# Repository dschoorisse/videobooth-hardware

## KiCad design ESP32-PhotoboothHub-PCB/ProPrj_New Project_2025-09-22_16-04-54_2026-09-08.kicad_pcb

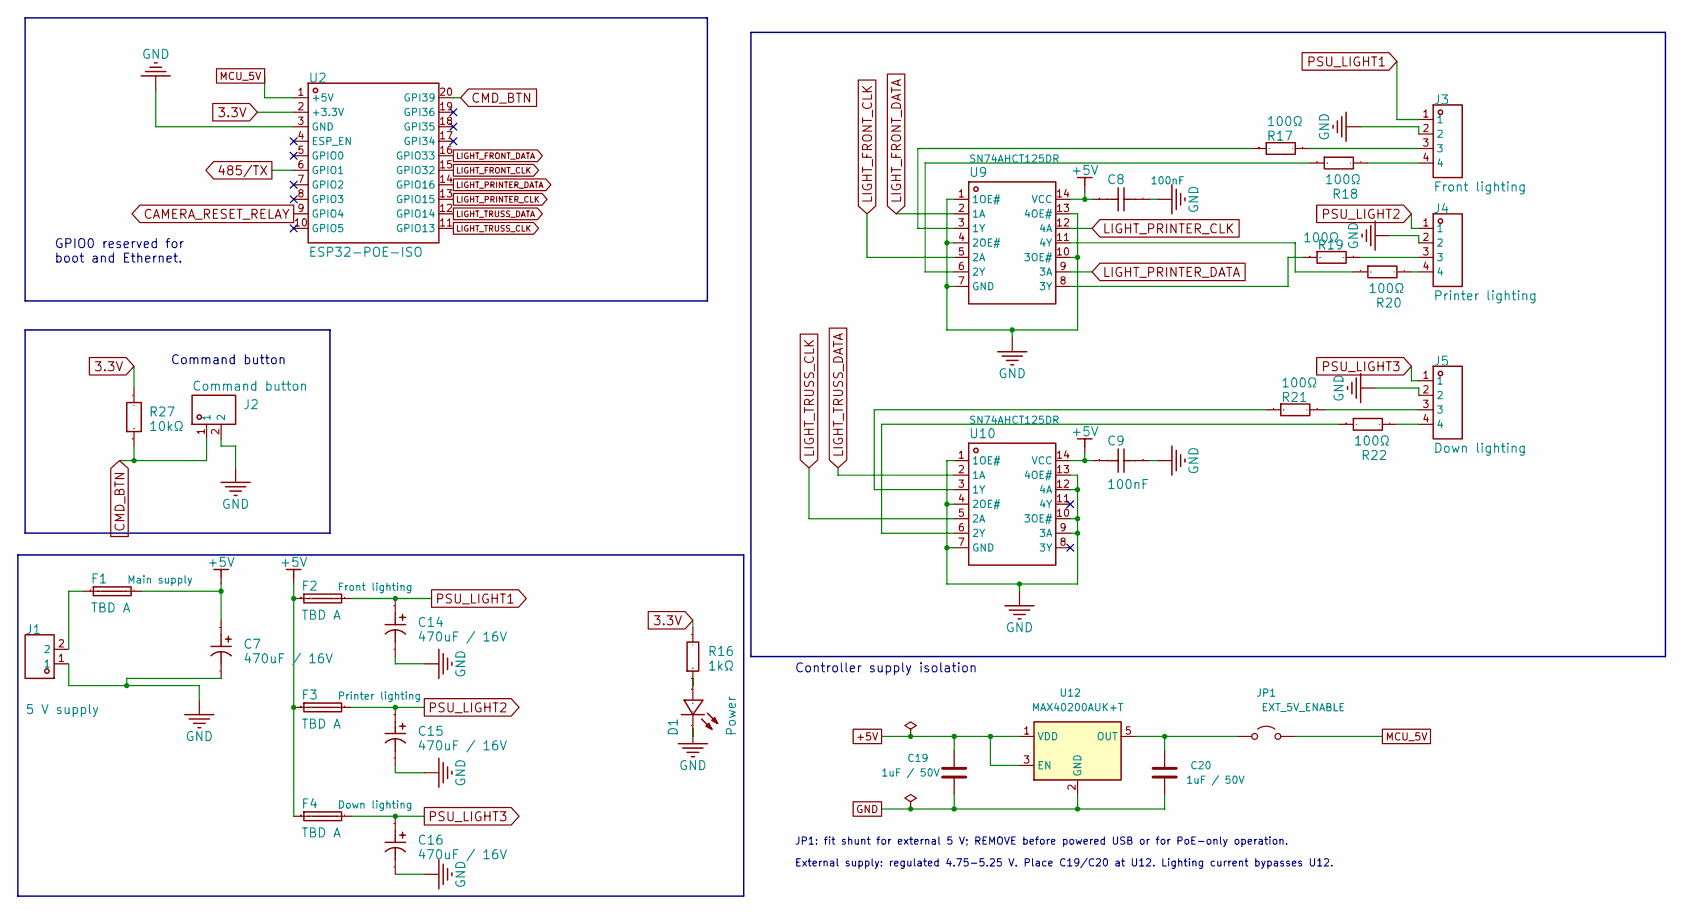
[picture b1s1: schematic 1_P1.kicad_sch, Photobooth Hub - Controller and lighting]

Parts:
C7, C14, C15, C16: 470uF / 16V; CP_Elec_8x10.5; Voltage Rating 16 V; Tolerance 20%; Manufacturer Part RVT1C471M0810; LCSC Part Name 470uF 16V aluminum electrolytic SMD 8x1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
C8, C9: 100nF; C_0603_1608Metric; Manufacturer Part CC0603KRX7R9BB104; LCSC Part Name 100nF ±10% 50V
C19, C20: 1uF / 50V; C_0603_1608Metric; Tolerance 10%; Voltage Rating 50 V; Manufacturer Part CL10A105KB8NNNC
D1: Power; LED_0805_2012Metric_A1K2; Manufacturer Part NCD0805R1; LCSC Part Name NCD0805R1
F1, F2, F3, F4: TBD A; Fuseholder_OptiFuse_CNT-06_MICRO2; Manufacturer Part CNT-06
J1: 5 V supply; PhoenixContact_SPT_1.5_2-V-3.5_1990850; Manufacturer Part 1990850
J2: Command button; PhoenixContact_SPT_1.5_2-V-3.5_1990850; Manufacturer Part 1990850
J3: Front lighting; PhoenixContact_SPT_1.5_4-V-3.5_1990876; Manufacturer Part 1990876
J4: Printer lighting; PhoenixContact_SPT_1.5_4-V-3.5_1990876; Manufacturer Part 1990876
J5: Down lighting; PhoenixContact_SPT_1.5_4-V-3.5_1990876; Manufacturer Part 1990876
JP1: EXT_5V_ENABLE; PinHeader_1x02_P2.54mm_Vertical; Manufacturer Part M20-9990246
R16: 1kΩ; R_0603_1608Metric; Manufacturer Part 0603WAF1001T5E; LCSC Part Name 1kΩ ±1% 100mW 厚膜电阻
R17, R18, R19, R20, R21, R22: 100Ω; R_0603_1608Metric; Manufacturer Part 0603WAF1000T5E; LCSC Part Name 100Ω ±1% 100mW 厚膜电阻
R27: 10kΩ; R_0603_1608Metric; Manufacturer Part 0603WAF1002T5E; LCSC Part Name 厚膜电阻 10kΩ ±1% 100mW
U2: ESP32-POE-ISO; Olimex_ESP32-POE-ISO; Manufacturer Part ESP32-POE-ISO; LCSC Part Name ESP32-POE-ISO
U9, U10: SN74AHCT125DR; SOIC-14_3.9x8.7mm_P1.27mm; Manufacturer Part SN74AHCT125DR; LCSC Part Name 三态输出，四路总线缓冲门
U12: MAX40200AUK+T; SOT-23-5; Manufacturer Part MAX40200AUK+T

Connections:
3.3V: R16.2, R27.2, U2.2 (+3.3V); also elsewhere on the board
485/TX: U2.6 (GPIO1); also elsewhere on the board
+5V: C7.1, C8.1, C9.1, C19.1, F1.2, F2.1, F3.1, F4.1, U9.14 (VCC), U10.14 (VCC), U12.1 (VDD), U12.3 (EN); also elsewhere on the board
CAMERA_RESET_RELAY: U2.9 (GPIO4); also elsewhere on the board
CMD_BTN: J2.1, R27.1, U2.20 (GPI39)
GND: C7.2, C8.2, C9.2, C14.2, C15.2, C16.2, C19.2, C20.2, D1.2 (-), J1.1, J2.2, J3.2, J4.2, J5.2, U2.3 (GND), U9.1 (1OE#), U9.4 (2OE#), U9.7 (GND), U9.10 (3OE#), U9.13 (4OE#), U10.1 (1OE#), U10.4 (2OE#), U10.7 (GND), U10.9 (3A), U10.10 (3OE#), U10.12 (4A), U10.13 (4OE#), U12.2 (GND); also elsewhere on the board
LIGHT_FRONT_CLK: U2.15 (GPIO32), U9.5 (2A)
LIGHT_FRONT_DATA: U2.16 (GPIO33), U9.2 (1A)
LIGHT_PRINTER_CLK: U2.13 (GPIO15), U9.12 (4A)
LIGHT_PRINTER_DATA: U2.14 (GPIO16), U9.9 (3A)
LIGHT_TRUSS_CLK: U2.11 (GPIO13), U10.5 (2A)
LIGHT_TRUSS_DATA: U2.12 (GPIO14), U10.2 (1A)
MCU_5V: JP1.2 (B), U2.1 (+5V)
unnamed: D1.1 (+), R16.1
unnamed: F1.1, J1.2
unnamed: J3.3, R17.2
unnamed: J3.4, R18.2
unnamed: J4.3, R19.2
unnamed: J4.4, R20.2
unnamed: J5.3, R21.2
unnamed: J5.4, R22.2
unnamed: C20.1, JP1.1 (A), U12.5 (OUT)
unnamed: R17.1, U9.3 (1Y)
unnamed: R18.1, U9.6 (2Y)
unnamed: R19.1, U9.8 (3Y)
unnamed: R20.1, U9.11 (4Y)
unnamed: R21.1, U10.3 (1Y)
unnamed: R22.1, U10.6 (2Y)
PSU_LIGHT1: C14.1, F2.2, J3.1
PSU_LIGHT2: C15.1, F3.2, J4.1
PSU_LIGHT3: C16.1, F4.2, J5.1

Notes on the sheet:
External supply: regulated 4.75-5.25 V. Place C19/C20 at U12. Lighting current bypasses U12.
JP1: fit shunt for external 5 V; REMOVE before powered USB or for PoE-only operation.
Command button
GPIO0 reserved for boot and Ethernet.
Controller supply isolation

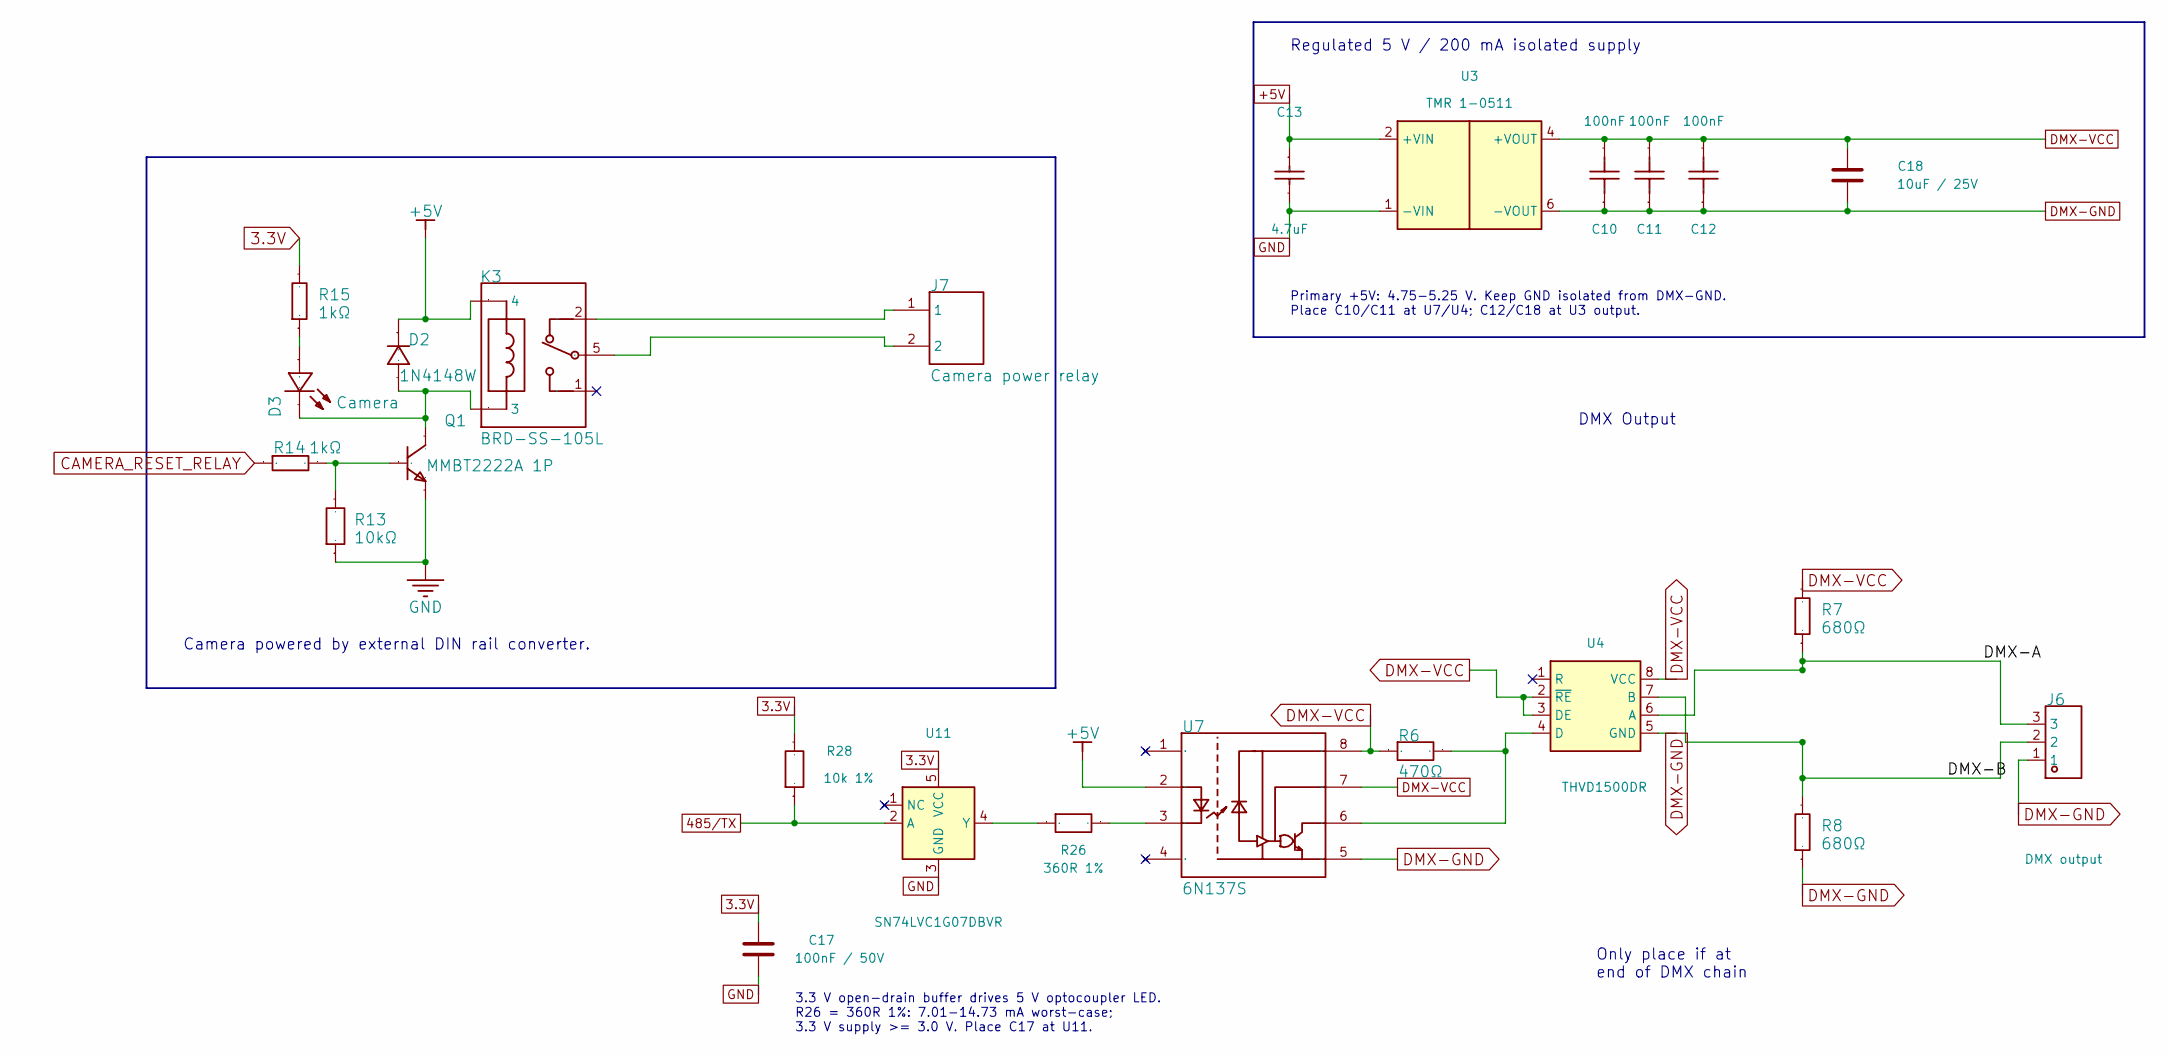
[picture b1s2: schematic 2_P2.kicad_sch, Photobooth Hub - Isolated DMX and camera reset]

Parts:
C10, C11, C12: 100nF; C_0603_1608Metric; Manufacturer Part CC0603KRX7R9BB104; LCSC Part Name 100nF ±10% 50V
C13: 4.7uF; C_0603_1608Metric; Manufacturer Part CL10A475KO8NNNC; LCSC Part Name 4.7uF ±10% 16V
C17: 100nF / 50V; C_0603_1608Metric; Voltage Rating 50 V; Manufacturer Part CC0603KRX7R9BB104
C18: 10uF / 25V; C_0805_2012Metric; Voltage Rating 25 V; Manufacturer Part CL21A106KAYNNNE
D2: 1N4148W; D_SOD-123; Manufacturer Part 1N4148W; LCSC Part Name 1N4148W
D3: Camera; LED_0805_2012Metric_A1K2; Manufacturer Part NCD0805R1; LCSC Part Name NCD0805R1
J6: DMX output; PhoenixContact_SPT_1.5_3-V-3.5_1990863; Manufacturer Part 1990863
J7: Camera power relay; PhoenixContact_SPT_1.5_2-V-3.5_1990850; Manufacturer Part 1990850
K3: BRD-SS-105L; Relay_SPDT_QLRELAY_BRD-SS-105L; Manufacturer Part BRD-SS-105L; LCSC Part Name 功率继电器
Q1: MMBT2222A 1P; SOT-23; Manufacturer Part MMBT2222A 1P; LCSC Part Name hFE：100-300 丝印1P
R6: 470Ω; R_0603_1608Metric; Manufacturer Part 0603WAF4700T5E; LCSC Part Name 470Ω ±1% 100mW 厚膜电阻
R7, R8: 680Ω; R_0603_1608Metric; Manufacturer Part 0603WAF6800T5E; LCSC Part Name 680Ω ±1% 100mW 厚膜电阻
R13: 10kΩ; R_0603_1608Metric; Manufacturer Part 0603WAF1002T5E; LCSC Part Name 厚膜电阻 10kΩ ±1% 100mW
R14, R15: 1kΩ; R_0603_1608Metric; Manufacturer Part 0603WAF1001T5E; LCSC Part Name 1kΩ ±1% 100mW 厚膜电阻
R26: 360R 1%; R_0603_1608Metric; Tolerance 1%; Manufacturer Part 0603WAF3600T5E
R28: 10k 1%; R_0603_1608Metric; Tolerance 1%; Manufacturer Part 0603WAF1002T5E
U3: TMR 1-0511; Converter_DCDC_TRACO_TMR-1-xxxx_Single_THT; Manufacturer Part TMR 1-0511
U4: THVD1500DR; SOIC-8_3.9x4.9mm_P1.27mm; Manufacturer Part THVD1500DR
U7: 6N137S; SMDIP-8_W9.53mm; Manufacturer Part 6N137S; LCSC Part Name 光耦
U11: SN74LVC1G07DBVR; SOT-23-5; Manufacturer Part SN74LVC1G07DBVR

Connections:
3.3V: C17.1, R15.2, R28.2, U11.5 (VCC); also elsewhere on the board
485/TX: R28.1, U11.2 (A); also elsewhere on the board
+5V: C13.1, D2.1 (C), K3.4, U3.2 (+VIN), U7.2 (A); also elsewhere on the board
/P2/DMX-A: J6.3, R7.1, U4.6 (A)
/P2/DMX-B: J6.2, R8.2, U4.7 (B)
CAMERA_RESET_RELAY: R14.1; also elsewhere on the board
DMX-GND: C10.1, C11.1, C12.1, C18.2, J6.1, R8.1, U3.6 (-VOUT), U4.5 (GND), U7.5 (GND)
DMX-VCC: C10.2, C11.2, C12.2, C18.1, R6.1, R7.2, U3.4 (+VOUT), U4.2 (~RE), U4.3 (DE), U4.8 (VCC), U7.7 (VE), U7.8 (VCC)
GND: C13.2, C17.2, Q1.2 (E), R13.1, U3.1 (-VIN), U11.3 (GND); also elsewhere on the board
unnamed: D2.2 (A), D3.2 (-), K3.3, Q1.3 (C)
unnamed: D3.1 (+), R15.1
unnamed: J7.1, K3.2
unnamed: J7.2, K3.5
unnamed: Q1.1 (B), R13.2, R14.2
unnamed: R6.2, U4.4 (D), U7.6 (VO)
unnamed: R26.2, U7.3 (C)
unnamed: R26.1, U11.4 (Y)

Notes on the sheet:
DMX Output
Primary +5V: 4.75-5.25 V. Keep GND isolated from DMX-GND. Place C10/C11 at U7/U4; C12/C18 at U3 output.
Only place if at end of DMX chain
Regulated 5 V / 200 mA isolated supply
Camera powered by external DIN rail converter.
3.3 V open-drain buffer drives 5 V optocoupler LED. R26 = 360R 1%: 7.01-14.73 mA worst-case; 3.3 V supply >= 3.0 V. Place C17 at U11.

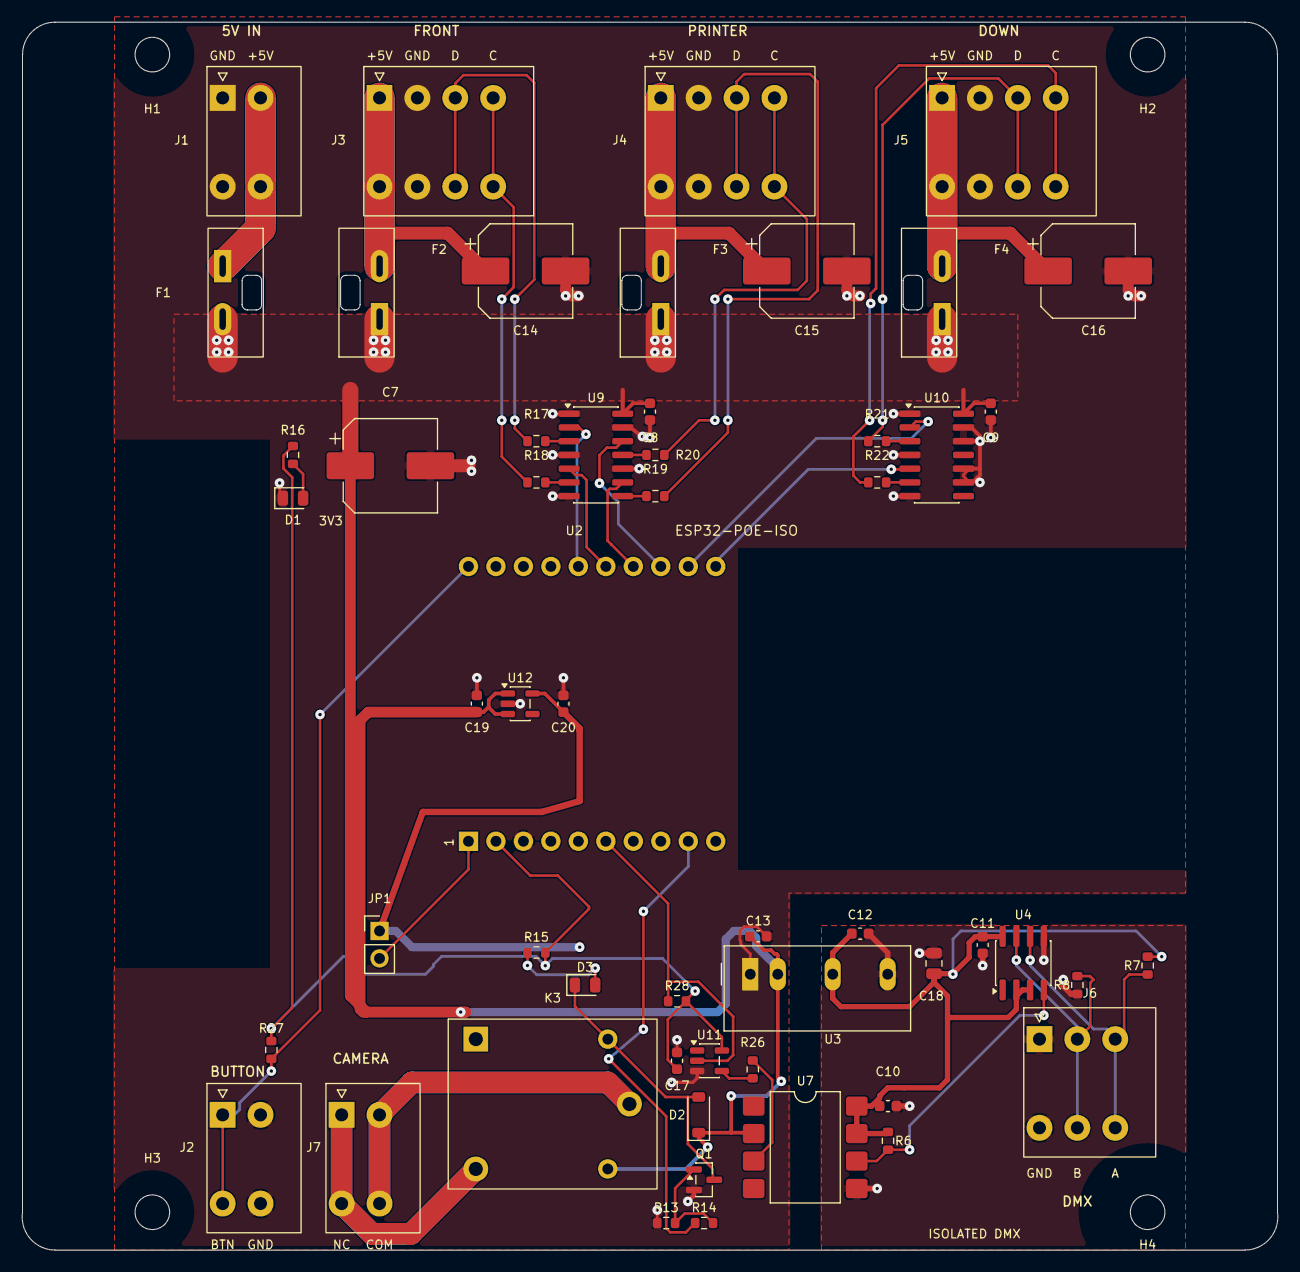
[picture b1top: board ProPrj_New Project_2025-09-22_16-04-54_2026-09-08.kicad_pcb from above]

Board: 2 copper layers, 116.1 x 113.5 mm, 59 parts (0 on the bottom side), 43 nets.

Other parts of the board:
H1, H2, H3, H4: M3 carrier mounting; MountingHole_3.2mm_M3

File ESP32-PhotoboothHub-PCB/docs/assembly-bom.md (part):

# Purchasing BOM and assembly items

Reconciled 13 September 2026 against the native KiCad 10.0.0
`current-20260913.xml` netlist, exported at 19:26:37 from the current schematic.
This includes the C8/C9 100 nF bypass selection and the selected JP1 header/shunt.
Quantities are **per completed carrier assembly**, before purchasing spares or
assembly attrition. Grouping uses manufacturer part number, independent of the
schematic's display value: C8/C9/C10/C11/C12/C17 form the 100 nF group;
C19/C20 form the 1 µF group.

The schematic has **56 physical references: 40 fitted SMT, 14 fitted THT,
one fitted Olimex module assembly, and one DNP resistor**. The 55 fitted
references do not equal the final purchased-item count: U2 needs mating
connectors, F1–F4 need fuse cartridges, and JP1 needs a separate shunt.

Supplier codes below are recorded identifiers, not a current-stock guarantee.
`Not selected` means the exact MPN is known but a distributor/order code is not
recorded. The assembly quote must confirm sourcing, package orientation,
attrition and manual-part handling. No production purchasing release is implied.

## Fitted SMT components

All rows in this table are **SMT assembly**. Total: **40 pieces, 19 MPN groups**.

| Qty | References | Component | Manufacturer | Exact MPN | Supplier / code |
|---:|---|---|---|---|---|
| 4 | C7, C14, C15, C16 | 470 µF, 16 V, ±20%, aluminum electrolytic | Honor Elec | `RVT1C471M0810` | LCSC `C3341` |
| 2 | C19, C20 | 1 µF, 50 V, ±10%, X5R, 0603 | Samsung | `CL10A105KB8NNNC` | LCSC `C15849` |
| 6 | C8, C9, C10, C11, C12, C17 | 100 nF, 50 V, ±10%, X7R, 0603 | Yageo | `CC0603KRX7R9BB104` | LCSC `C14663` |
| 1 | C13 | 4.7 µF, 16 V, ±10%, X5R, 0603 | Samsung | `CL10A475KO8NNNC` | LCSC `C19666` |
| 1 | C18 | 10 µF, 25 V, ±10%, X5R, 0805 | Samsung | `CL21A106KAYNNNE` | LCSC `C15850` |
| 2 | D1, D3 | Red 0805 indicator LED | Nationstar / 国星光电 | `NCD0805R1` | LCSC `C84256` |
| 1 | D2 | Switching diode, SOD-123 | ST / 先科 (Semtech) | `1N4148W` | LCSC `C81598` |
| 1 | Q1 | NPN transistor, SOT-23 | CJ / 江苏长电/长晶 | `MMBT2222A 1P` | LCSC `C8512` |
| 1 | R6 | 470 Ω, ±1%, 0.1 W, 0603 | UNI-ROYAL | `0603WAF4700T5E` | LCSC `C23179` |
| 2 | R7, R8 | 680 Ω, ±1%, 0.1 W, 0603 | UNI-ROYAL | `0603WAF6800T5E` | LCSC `C23228` |
| 3 | R13, R27, R28 | 10 kΩ, ±1%, 0.1 W, 0603 | UNI-ROYAL | `0603WAF1002T5E` | LCSC `C25804` |
| 3 | R14, R15, R16 | 1 kΩ, ±1%, 0.1 W, 0603 | UNI-ROYAL | `0603WAF1001T5E` | LCSC `C21190` |
| 6 | R17, R18, R19, R20, R21, R22 | 100 Ω, ±1%, 0.1 W, 0603 | UNI-ROYAL | `0603WAF1000T5E` | LCSC `C22775` |
| 1 | R26 | 360 Ω, ±1%, 0.1 W, 0603 | UNI-ROYAL | `0603WAF3600T5E` | LCSC `C25194` |
| 1 | U4 | 5 V RS-485 transceiver, SOIC-8 | Texas Instruments | `THVD1500DR` | Not selected |
| 1 | U7 | High-speed optocoupler, SMDIP-8 | UMW | `6N137S` | LCSC `C5123515` |
| 2 | U9, U10 | Quad AHCT buffer, SOIC-14 | Texas Instruments | `SN74AHCT125DR` | LCSC `C155176` |
| 1 | U11 | Open-drain buffer, SOT-23-5 | Texas Instruments | `SN74LVC1G07DBVR` | Not selected |
| 1 | U12 | Ideal diode, SOT-23-5 | Analog Devices | `MAX40200AUK+T` | Not selected |

D1/D3 use the project footprint's **pad 1 anode / pad 2 cathode** convention;
check placement polarity against that footprint. D2's supplier branding must
not be interpreted as STMicroelectronics. Preserve the exact U12 `+T` ordering
suffix and other recorded package suffixes when placing an order.

The four C3341 electrolytics are standard catalog SMT parts but were verified
as **JLCPCB Extended**, so additional loading fees may apply. Other recorded
LCSC codes do not imply Basic classification, current stock, or automatic
availability at PCBWay/Aisler. Component sources and dimensions are in
[remaining-component-footprints.md](remaining-component-footprints.md).

## Fitted through-hole components and module

The first seven rows total **14 THT pieces**. U2 is a separate assembled module,
installed after carrier soldering; its two carrier sockets are additional
purchased items in the accessory table.

| Qty | References | Component | Manufacturer | Exact MPN | Supplier / code | Assembly |
|---:|---|---|---|---|---|---|
| 4 | F1, F2, F3, F4 | Vertical MICRO2-style **holder only**, 15 A holder rating | OptiFuse | `CNT-06` | OptiFuse `CNT-06` | Manual THT; insert separate fuse afterward |
| 3 | J1, J2, J7 | 2-pole vertical spring terminal | Phoenix Contact | `1990850` — SPT 1,5/2-V-3,5 | Phoenix Contact `1990850` | THT |
| 1 | J6 | 3-pole vertical spring terminal | Phoenix Contact | `1990863` — SPT 1,5/3-V-3,5 | Phoenix Contact `1990863` | THT |
| 3 | J3, J4, J5 | 4-pole vertical spring terminal | Phoenix Contact | `1990876` — SPT 1,5/4-V-3,5 | Phoenix Contact `1990876` | THT |
| 1 | JP1 | 1×2, 2.54 mm vertical header; shunt separate | Harwin | `M20-9990246` | Distributor not selected | THT |
| 1 | K3 | 5 V SPDT relay | QLRELAY | `BRD-SS-105L` | LCSC `C22384955` | THT |
| 1 | U3 | Regulated isolated 5 V / 200 mA converter | TRACO POWER | `TMR 1-0511` | LCSC `C7362907` | THT SIP |
| 1 | U2 | 98 mm ESP32 module board | Olimex | `ESP32-POE-ISO` | LCSC `C19104183` | Module installation; mating hardware separate |

The `CNT-06` supplier entry is the manufacturer's order identifier, not an
LCSC code. The same applies to Phoenix order numbers. Manufacturer availability
and through-hole assembly must be confirmed with the chosen supplier/assembler.

## Do not populate

| Fitted qty | References | Component | Manufacturer | Exact MPN | Supplier / code | Assembly |
|---:|---|---|---|---|---|---|
| 0 | R9 | 120 Ω, ±1%, 0.1 W, 0603; optional DMX termination | UNI-ROYAL | `0603WAF1200T5E` | LCSC `C22787` | **DNP**; one PCB position exists |

Do not let a generic exporter turn R9 into a fitted purchasing quantity of one.
Its PCB pads remain available for an explicitly chosen termination configuration.

## Additional purchased items

These lines supplement the schematic BOM; they do not add electrical references
or duplicate the header/holder/module already counted above.

| Qty per assembly | Associated reference | Item / proposed MPN | Selection and assembly status |
|---:|---|---|---|
| 1 | JP1 | Harwin **`M7566-46`** red removable shunt | Selected matching accessory; purchase separately from JP1 header. Distributor code not selected. |
| 1 | F1 | OptiFuse ANT/APT main-supply fuse, exact suffix **TBD** | Select current/time-current behavior from load, inrush, wiring and copper. CNT-06 is only the holder. |
| 1 | F2 | OptiFuse ANT/APT front-light fuse, exact suffix **TBD** | Branch load/inrush not yet specified. |
| 1 | F3 | OptiFuse ANT/APT printer-light fuse, exact suffix **TBD** | Branch load/inrush not yet specified. |
| 1 | F4 | OptiFuse ANT/APT down-light fuse, exact suffix **TBD** | Branch load/inrush not yet specified. |
| 2 | U2 carrier connection | 1×10 female THT socket strips, 2.54 mm pitch, nominal 8.5 mm body height; MPN **TBD** | Intended removable mounting. Rows are 25.40 mm apart. Select pin acceptance, insertion depth, tail geometry and plating together with the module headers. Solder these sockets to the carrier. |
| 0 or 2 | U2 module connection | 1×10 downward-facing male headers, 2.54 mm pitch; MPN **TBD** | Inspect the actual Olimex module: buy two only if suitable headers are not already fitted. Solder to the module if required; do not solder the module directly to the carrier. |
| TBD | U2 mounting guides | Module standoffs, screws and related hardware | Select after socket stack height and fastening arrangement are fixed; do not infer a fastener kit from the drawing guides alone. |
| TBD | Carrier mounting | Enclosure/DIN mounting hardware and carrier fasteners | Board mounting arrangement and enclosure not finalized. No screw length or spacer height selected. |
| 1 | Carrier | Fabricated bare PCB | Supply approved layout/stackup and fabrication files when ready; artwork is not a purchased schematic component. |

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
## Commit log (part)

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2025-05-27 combine printer lights with internal LED lights for lighting of the subject
2025-05-27 remove the separate printer light
2025-06-06 added stub for Windows installation and configuration instructions
2025-09-09 updated claude config
2025-10-20 Enhance PhotoboothHub configuration with DMX support, multiple SPI buses, and improved shutdown button functionality
